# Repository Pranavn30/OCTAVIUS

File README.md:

# OCTAVIUS
Creating hardware for implantation for the goal of recording neural data to create multidimensional next-gen prosthetics

Portfolio Examples:

Firmware:
- Firmware -> main.c
- Firmware -> intan.c
- Firmware -> init.c

PCB:
- Octopus PCB -> OCTOBOARDV_1.1
- Octopus PCB -> OCTOBOARDV_1.2
- HORNET PCB -> HIVE_dev_sc

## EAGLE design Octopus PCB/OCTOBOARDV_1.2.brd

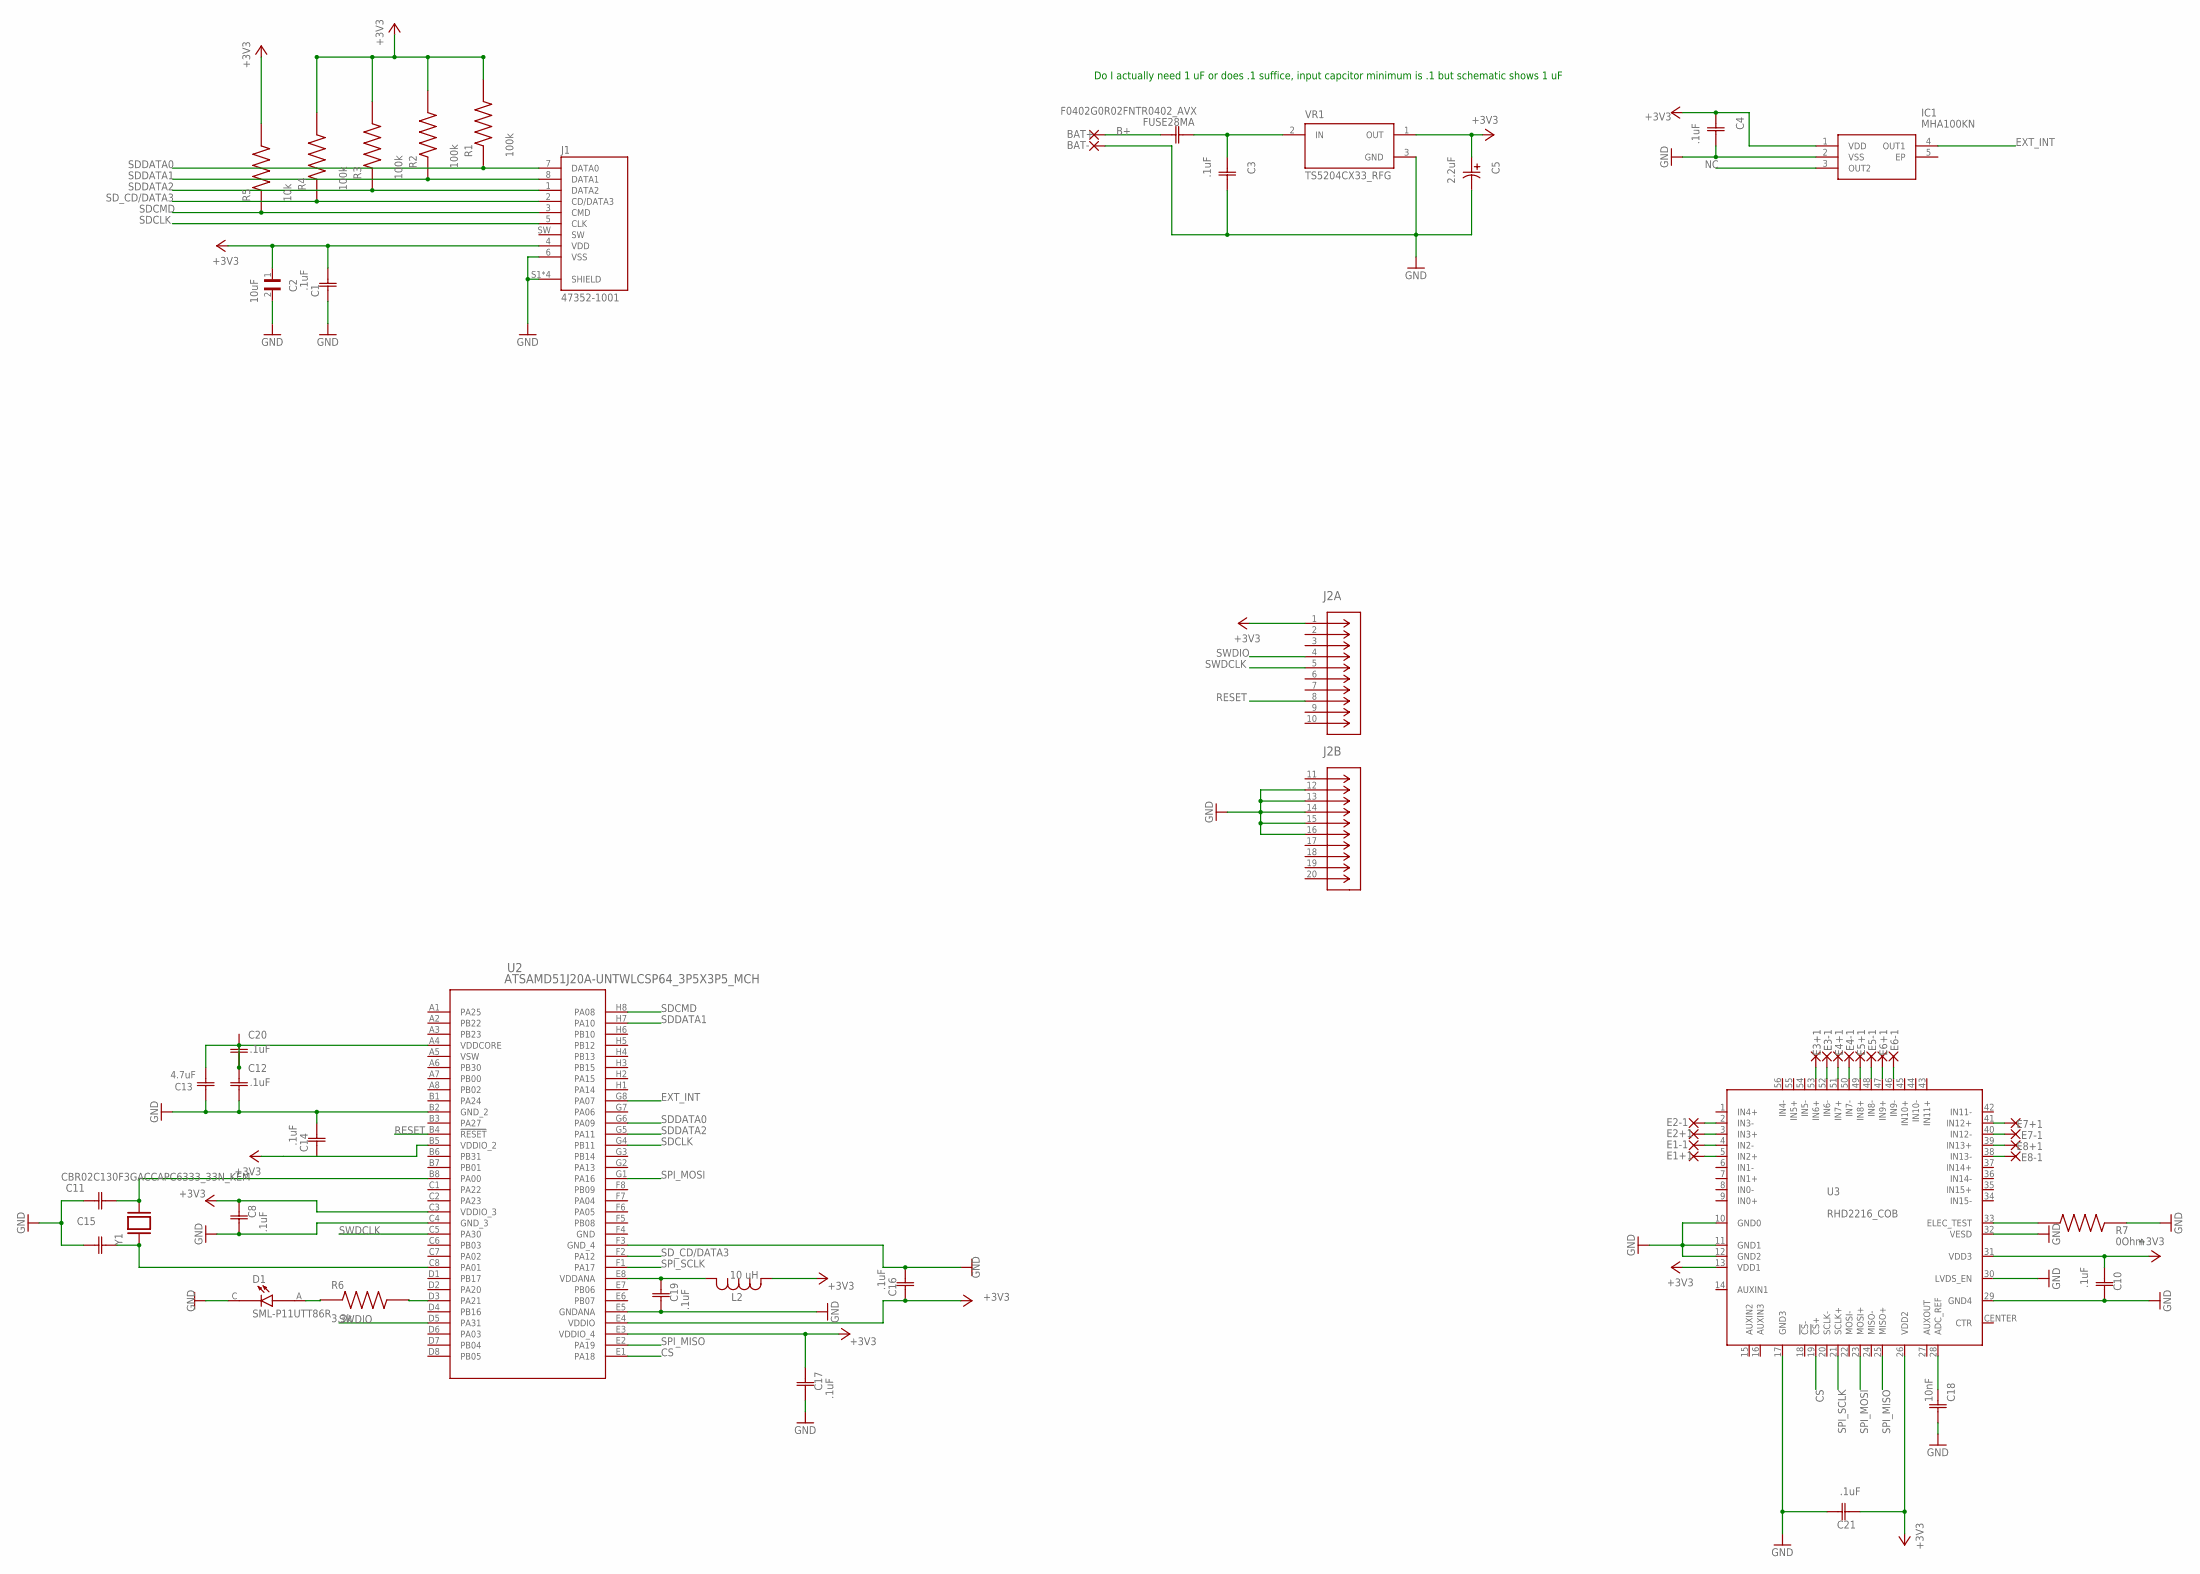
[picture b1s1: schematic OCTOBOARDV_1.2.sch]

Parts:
BAT+: 1.36/.71LEAD; 1,6/0,9
BAT-: 1.36/.71LEAD; 1,6/0,9
C1, C3, C4, C8, C10, C12, C14, C16, C17, C19, C20, C21: .1uF; CAP_0402_WAL
C2: 10uF; CAPC1005X70N
C5: 2.2uF; CAPMP3.4X1.6_1.8N_KEM
C11, C15: CBR02C130F3GACCAPC6333_33N_KEM; CAPC6333_33N_KEM
C13: 4.7uF; CAP_CM03_F_KAV
C18: 10nF; CAP_00J25AH_AVX
D1: SML-P11UTT86R; LED_SML-P11UTT86R
E1+1, E1-1, E2+1, E2-1, E3+1, E3-1, E4+1, E4-1, E5+1, E5-1, E6+1, E6-1, E7+1, E7-1, E8+1, E8-1: 1.36/.71LEAD; 1,6/0,9
FUSE28MA: F0402G0R02FNTR0402_AVX; 0402_AVX
IC1: MHA100KN
J1: 47352-1001; MOLEX_47352-1001
J2: PRPC040DAAN-RCCONN80_PRP-040_4000X197_SUL; CONN80_PRP-040_4000X197_SUL
L2: 10 uH; IND_SDEB12101T_CYN
R1, R2, R3, R4: 100k; RES_ERJ1GNJ104C
R5: 10k; RES_ERJ-1RHD1002C
R6: 3.3k; RESC0603X26N
R7: 0Ohm; RESC0603X26N
U2: ATSAMD51J20A-UNTWLCSP64_3P5X3P5_MCH; WLCSP64_3P5X3P5_MCH
U3: RHD2216_COB; RHD2000_56PIN_COB
VR1: TS5204CX33_RFG; SOT95P280X110-3N
Y1: CM9V-T1A-32.768KHZ-9PF-20PPM-TA-QC; XTAL_CM9V-T1A-32.768KHZ-9PF-20PPM-TA-QC

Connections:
+3V3: C1.2, C2.1, C4.1, C5.1, C8.1, C10.1, C17.1, C21.1, IC1.1 (VDD), J1.4 (VDD), J2.1, L2.2, R1.2, R2.2, R3.2, R4.2, R5.2, U2.C3 (VDDIO_3), U2.E3 (VDDIO_4), U3.13 (VDD1), U3.26 (VDD2), U3.31 (VDD3), VR1.1 (OUT)
B+: BAT+.1, FUSE28MA.1 (11)
CS: U2.E1 (PA18), U3.19 (!CS!+)
CTR: U3.CENTER (CTR)
EXT_INT: IC1.4 (OUT1), U2.G8 (PA07)
GND: BAT-.1, C1.1, C2.2, C3.2, C4.2, C5.2, C8.2, C10.2, C11.1, C12.2, C13.2, C14.2, C15.1, C17.2, C18.2, C19.2, C21.2, D1.C, IC1.2 (VSS), J1.6 (VSS), J1.S1 (SHIELD), J1.S2 (SHIELD), J1.S3 (SHIELD), J1.S4 (SHIELD), J2.12 (42), J2.13 (43), J2.14 (44), J2.15 (45), J2.16 (46), R7.2, U2.B2 (GND_2), U2.C4 (GND_3), U2.E5 (GNDANA), U3.10 (GND0), U3.11 (GND1), U3.12 (GND2), U3.17 (GND3), U3.29 (GND4), U3.30 (LVDS_EN), U3.32 (VESD), VR1.3 (GND)
unnamed: C3.1, FUSE28MA.2 (12), VR1.2 (IN)
unnamed: C18.1, U3.28 (ADC_REF)
unnamed: D1.A, R6.1
unnamed: C11.2, U2.B8 (PA00), Y1.2
unnamed: R6.2, U2.D3 (PA21)
unnamed: C15.2, U2.C8 (PA01), Y1.1
unnamed: R7.1, U3.33 (ELEC_TEST)
unnamed: E1+1.1, U3.5 (IN2+)
unnamed: E1-1.1, U3.4 (IN2-)
unnamed: E2+1.1, U3.3 (IN3+)
unnamed: E2-1.1, U3.2 (IN3-)
unnamed: E3+1.1, U3.53 (IN6+)
unnamed: E3-1.1, U3.52 (IN6-)
unnamed: E4+1.1, U3.51 (IN7+)
unnamed: E4-1.1, U3.50 (IN7-)
unnamed: E5+1.1, U3.49 (IN8+)
unnamed: C19.1, L2.1, U2.E8 (VDDANA)
unnamed: C16.2, U2.F3 (GND_4)
unnamed: C16.1, U2.E4 (VDDIO)
unnamed: C12.1, C13.1, C20.2, U2.A4 (VDDCORE)
unnamed: E5-1.1, U3.48 (IN8-)
unnamed: E6+1.1, U3.47 (IN9+)
unnamed: C14.1, U2.B5 (VDDIO_2)
unnamed: E6-1.1, U3.46 (IN9-)
unnamed: E7+1.1, U3.41 (IN12+)
unnamed: E7-1.1, U3.40 (IN12-)
unnamed: E8+1.1, U3.39 (IN13+)
unnamed: E8-1.1, U3.38 (IN13-)
NC: IC1.3 (OUT2)
RESET: J2.8, U2.B4 (!RESET)
SDCLK: J1.5 (CLK), U2.G4 (PB11)
SDCMD: J1.3 (CMD), R5.1, U2.H8 (PA08)
SDDATA0: J1.7 (DATA0), R1.1, U2.G6 (PA09)
SDDATA1: J1.8 (DATA1), R2.1, U2.H7 (PA10)
SDDATA2: J1.1 (DATA2), R3.1, U2.G5 (PA11)
SD_CD/DATA3: J1.2 (CD/DATA3), R4.1, U2.F2 (PA12)
SPI_MISO: U2.E2 (PA19), U3.25 (MISO+)
SPI_MOSI: U2.G1 (PA16), U3.23 (MOSI+)
SPI_SCLK: U2.F1 (PA17), U3.21 (SCLK+)
SWDCLK: J2.5, U2.C5 (PA30)
SWDIO: J2.4, U2.D5 (PA31)

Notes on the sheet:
Do I actually need 1 uF or does .1 suffice, input capcitor minimum is .1 but schematic shows 1 uF

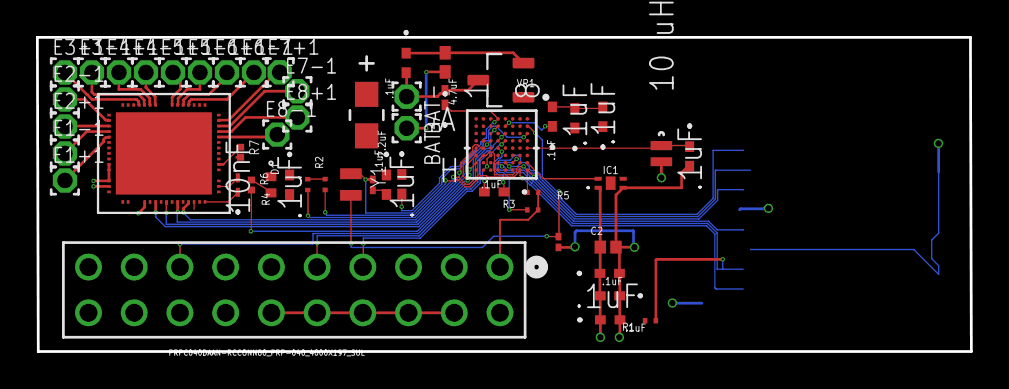
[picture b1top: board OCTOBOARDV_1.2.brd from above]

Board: 4 copper layers, 51.9 x 17.5 mm, 53 parts (1 on the bottom side), 45 nets.

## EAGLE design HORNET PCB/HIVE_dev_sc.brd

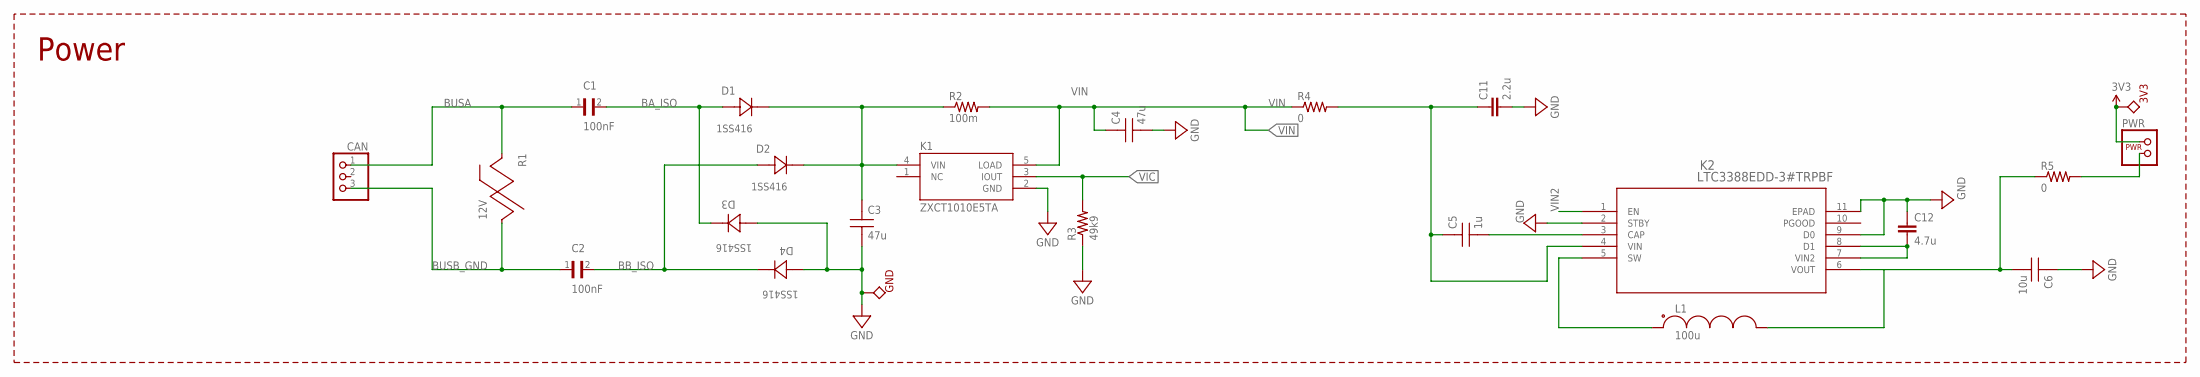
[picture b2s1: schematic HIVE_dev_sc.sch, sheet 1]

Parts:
3V3: TPTP5001; TP5000OR5001
C1, C2: 100nF; CAPC1005X55N
C3, C4: 47u; C0603
C5: 1u; C0201
C6: 10u; C0603
C11: 2.2u; 0402
C12: 4.7u; 0402
CAN: PINHD-1X3; 1X03
D1, D2, D3, D4: 1SS416; SOD-923_TOS
GND: TPTP5001; TP5000OR5001
K1: ZXCT1010E5TA; SOT25
K2: LTC3388EDD-3#TRPBF; DFN-10_DD
L1: 100u; LPS4414
PWR: POWERJUMP; 1X04
R1: 12V; CG0603MLC
R2: 100m; R0201
R3: 49k9; 0201
R4, R5: 0; R0201

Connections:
3V3: 3V3.P$1, PWR.1, PWR.2 (1); also elsewhere on the board
BA_ISO: C1.2, D1.2 (ANODE), D3.1 (CATHODE)
BB_ISO: C2.2, D2.2 (ANODE), D4.1 (CATHODE)
BUSA: C1.1, CAN.1, R1.1; also elsewhere on the board
BUSB_GND: C2.1, CAN.3, R1.2; also elsewhere on the board
GND: C3.1, C4.1, C6.2, C11.2, C12.1, D3.2 (ANODE), D4.2 (ANODE), GND.P$1, K1.2 (GND), K2.2 (STBY), K2.9 (D0), K2.11 (EPAD), R3.1; also elsewhere on the board
unnamed: C5.2, C11.1, K2.4 (VIN), R4.2
unnamed: C12.2, K2.7 (VIN2), K2.8 (D1)
unnamed: C6.1, K2.6 (VOUT), L1.P$2, R5.1
unnamed: C5.1, K2.3 (CAP)
unnamed: C3.2, D1.1 (CATHODE), D2.1 (CATHODE), K1.4 (VIN), R2.1
unnamed: K2.5 (SW), L1.P$1
unnamed: PWR.3 (2), PWR.4 (2), R5.2
VIC: K1.3 (IOUT), R3.2; also elsewhere on the board
VIN: C4.2, K1.5 (LOAD), R2.2, R4.1; also elsewhere on the board
VIN2: K2.1 (EN); also elsewhere on the board

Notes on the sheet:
Power

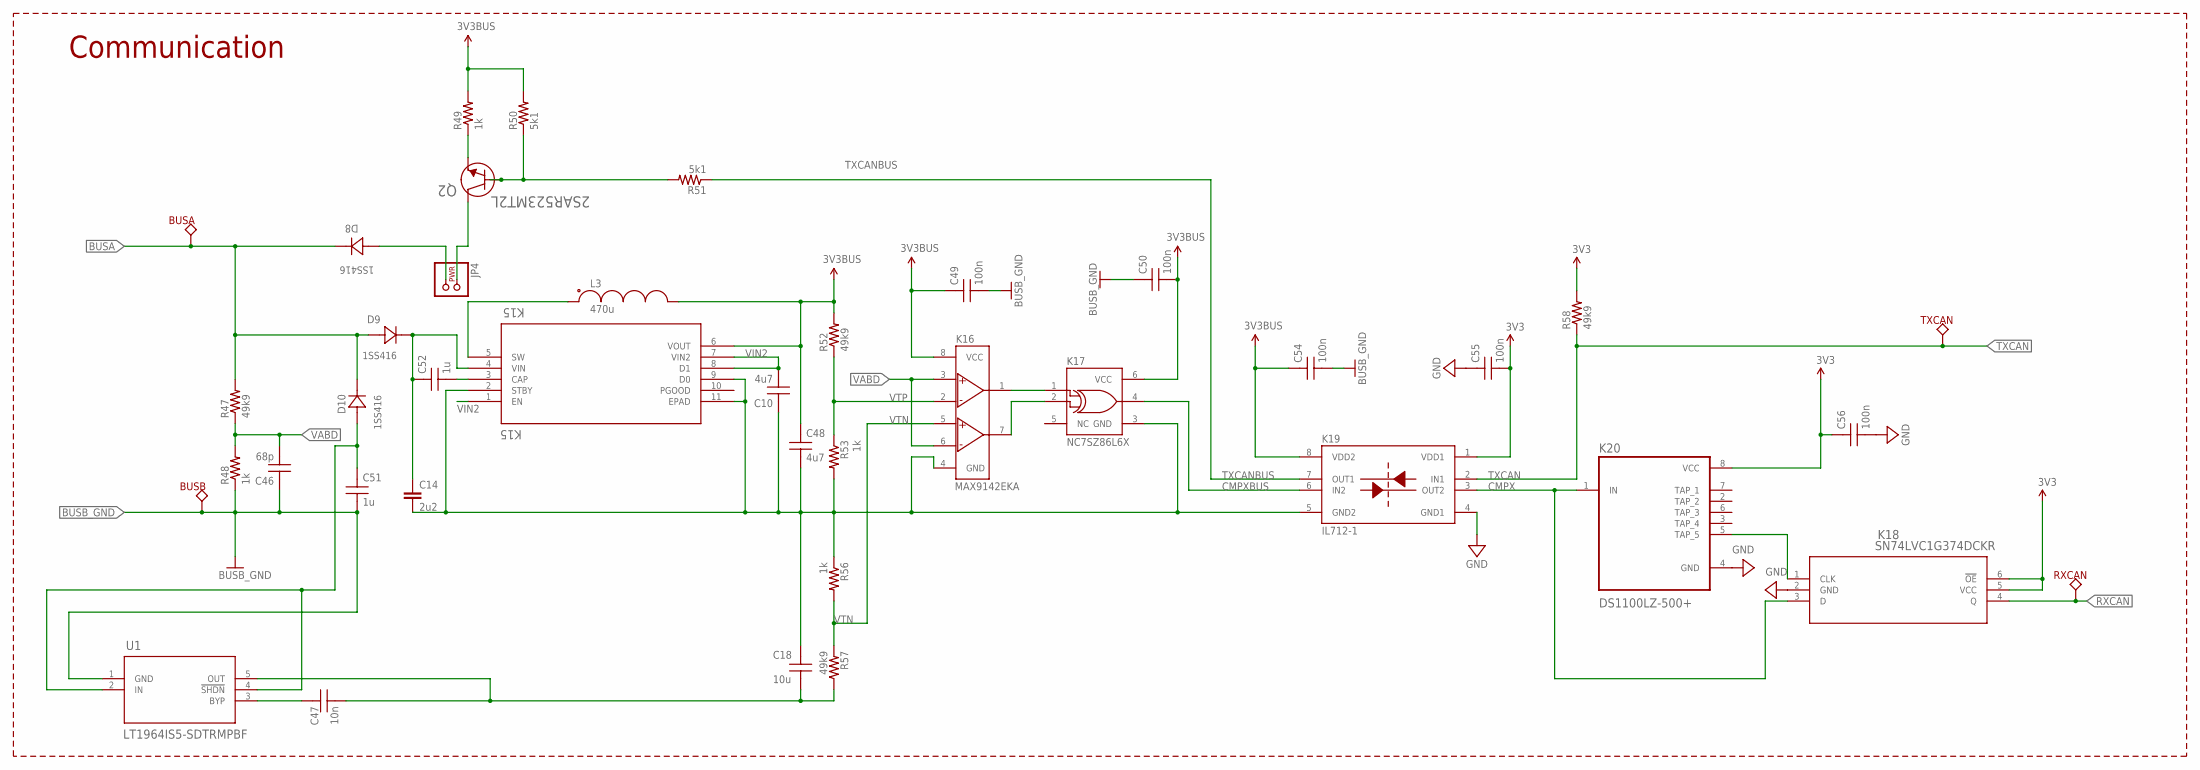
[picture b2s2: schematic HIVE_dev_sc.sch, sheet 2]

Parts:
BUSA: TPTP5001; TP5000OR5001
BUSB: TPTP5001; TP5000OR5001
C10, C48: 4u7; C0402
C14: 2u2; 0402
C18: 10u; C0201
C46: 68p; C0201
C47: 10n; C0201
C49, C50, C54, C55, C56: 100n; C0201
C51, C52: 1u; C0201
D8, D9, D10: 1SS416; SOD-923_TOS
JP4: POWERJUMP; 1X04
K15: K15; DFN-10_DD
K16: MAX9142EKA; SOT23-8
K17: NC7SZ86L6X; MAC06A
K18: SN74LVC1G374DCKR; DCK6
K19: IL712-1; MSOP-8
K20: DS1100LZ-500+; SOIC127P600X175-8N
L3: 470u; CB2518
Q2: 2SAR523MT2L; TRANS_2SAR522M_ROM
R47, R52, R57, R58: 49k9; 0201
R48, R49, R53, R56: 1k; 0201
R50, R51: 5k1; 0201
RXCAN: TPTP5001; TP5000OR5001
TXCAN: TPTP5001; TP5000OR5001
U1: LT1964IS5-SDTRMPBF; TSOT23-5_S5_ADI

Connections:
3V3: C55.1, C56.2, K18.5 (VCC), K18.6 (!OE), K19.1 (VDD1), K20.8 (VCC), R58.2; also elsewhere on the board
3V3BUS: C48.2, C49.2, C50.1, C54.2, K15.6 (VOUT), K16.8 (VCC), K17.6 (VCC), K19.8 (VDD2), L3.2, R49.2, R50.2, R52.2
3V3BUS2: JP4.1, JP4.2 (1), Q2.1 (COLLECTOR)
BUSA: BUSA.P$1, D8.1 (CATHODE), D9.2 (ANODE), D10.1 (CATHODE), R47.2; also elsewhere on the board
BUSB_GND: BUSB.P$1, C46.2, C49.1, C50.2, C51.1, C54.1, R48.1, U1.1 (GND); also elsewhere on the board
CMPX: K18.3 (D), K19.3 (OUT2), K20.1 (IN)
CMPXBUS: K17.4 (Y), K19.6 (IN2)
GND: C55.2, C56.1, K18.2 (GND), K19.4 (GND1), K20.4 (GND); also elsewhere on the board
unnamed: K15.5 (SW), L3.1
unnamed: C10.2, C14.2, C18.2, C48.1, K15.2 (STBY), K15.9 (D0), K15.11 (EPAD), K16.4 (GND), K17.3 (GND), K19.5 (GND2), R53.2, R56.1
unnamed: C52.1, K15.3 (CAP)
unnamed: K18.1 (CLK), K20.5 (TAP_5)
unnamed: Q2.3 (EMITTER), R49.1
unnamed: C47.2, U1.3 (BYP)
unnamed: C14.1, C52.2, D9.1 (CATHODE), K15.4 (VIN)
unnamed: C51.2, D10.2 (ANODE), U1.2 (IN), U1.4 (!SHDN)
unnamed: C18.1, C47.1, R57.1, U1.5 (OUT)
unnamed: Q2.2 (BASE), R50.1, R51.2
unnamed: K16.1 (OUT1), K17.1 (A)
unnamed: K16.7 (OUT2), K17.2 (B)
unnamed: D8.2 (ANODE), JP4.3 (2), JP4.4 (2)
RXCAN: K18.4 (Q), RXCAN.P$1; also elsewhere on the board
TXCAN: K19.2 (IN1), R58.1, TXCAN.P$1; also elsewhere on the board
TXCANBUS: K19.7 (OUT1), R51.1
VABD: C46.1, K16.3 (+IN1), K16.6 (-IN2), R47.1, R48.2
VIN2: C10.1, K15.1 (EN), K15.7 (VIN2), K15.8 (D1); also elsewhere on the board
VTN: K16.5 (+IN2), R56.2, R57.2
VTP: K16.2 (-IN1), R52.1, R53.1

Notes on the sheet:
Communication

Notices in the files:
parts and their libraries:
COPYRIGHT: Copyright (C) 2022 Ultra Librarian. All rights reserved.
COPYRIGHT: Copyright (C) 2023 Ultra Librarian. All rights reserved.
